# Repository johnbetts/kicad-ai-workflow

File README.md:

# kicad-ai-pipeline

AI-assisted KiCad EDA pipeline that takes hardware projects from natural-language requirements through to production-ready manufacturing files (Gerbers, BOM, CPL) for JLCPCB.

## What it does

1. **Requirements** — Define your board in plain English: components, connections, constraints
2. **Schematic** — Generates KiCad 10 hierarchical schematics with correct net assignment
3. **PCB Layout** — Places components using a 3-level EE-grade placement optimizer (zone partitioning, group placement, subcircuit refinement)
4. **Validation** — DRC, ERC, electrical checks, manufacturing checks, signal integrity
5. **Production** — Gerber, drill, BOM, CPL files ready for JLCPCB SMT assembly

Every stage outputs valid KiCad 10 files that open directly in KiCad.

## Install

```bash
pip install -e .
# or with dev dependencies:
pip install -e ".[dev]"
```

Requires Python 3.10+. No runtime dependencies for core pipeline.

## Quick start

```bash
# From a requirements JSON file:
kicad-pipeline build requirements.json --output-dir output/

# Or use the Python API:
python -c "
from kicad_pipeline.pcb.builder import build_pcb
from kicad_pipeline.models.requirements import ProjectRequirements
import json

req = ProjectRequirements.from_dict(json.load(open('requirements.json')))
pcb = build_pcb(req)
"
```

## Pipeline stages

| Stage | Module | Output |
|-------|--------|--------|
| Requirements | `requirements/` | `ProjectRequirements` dataclass |
| Parts enrichment | `parts/` | LCSC part numbers from JLCPCB 7M-part database |
| Schematic | `schematic/` | `.kicad_sch` files (hierarchical) |
| PCB layout | `pcb/` + `optimization/` | `.kicad_pcb` with placed components |
| Routing | `routing/` | Tracks and vias (grid router + FreeRouting) |
| Validation | `validation/` | DRC, ERC, electrical, manufacturing, thermal, SI reports |
| Production | `production/` | Gerbers, drill, BOM, CPL, assembly drawings |

## Project structure

```
src/kicad_pipeline/
  models/          # Frozen dataclasses: PCBDesign, ProjectRequirements, etc.
  sexp/            # KiCad S-expression parser and writer
  requirements/    # NL decomposition, component DB, pin/power budgets
  schematic/       # Schematic builder, symbols, subcircuits, wiring, ERC
  pcb/             # PCB builder, footprints, placement, netlist, zones
  optimization/    # EE placement optimizer (24 phases), scoring, review agent
  routing/         # Grid router, FreeRouting integration, DSN export
  validation/      # DRC, electrical, manufacturing, thermal, signal integrity
  production/      # Gerber, drill, BOM, CPL, assembly drawing, packager
  orchestrator/    # Multi-stage workflow engine with variant support
  github/          # Git ops, issues, releases, changelog
  cli/             # Command-line interface
tests/             # 2850+ tests (unit, integration, regression)
```

## Testing

```bash
pytest tests/ -x --tb=short          # Full suite
pytest tests/ -m "not slow"          # Fast tests only
pytest tests/ --cov=src/kicad_pipeline  # With coverage
```

## Code quality

```bash
mypy src/ --strict    # Type checking
ruff check src/ tests/  # Linting
ruff format src/ tests/ # Formatting
```

## JLCPCB compatibility

All components are validated against JLCPCB's parts catalog. The pipeline prefers basic parts (no setup fee) and verifies stock availability before generating production files.

## License

Apache License 2.0 — see [LICENSE](LICENSE).

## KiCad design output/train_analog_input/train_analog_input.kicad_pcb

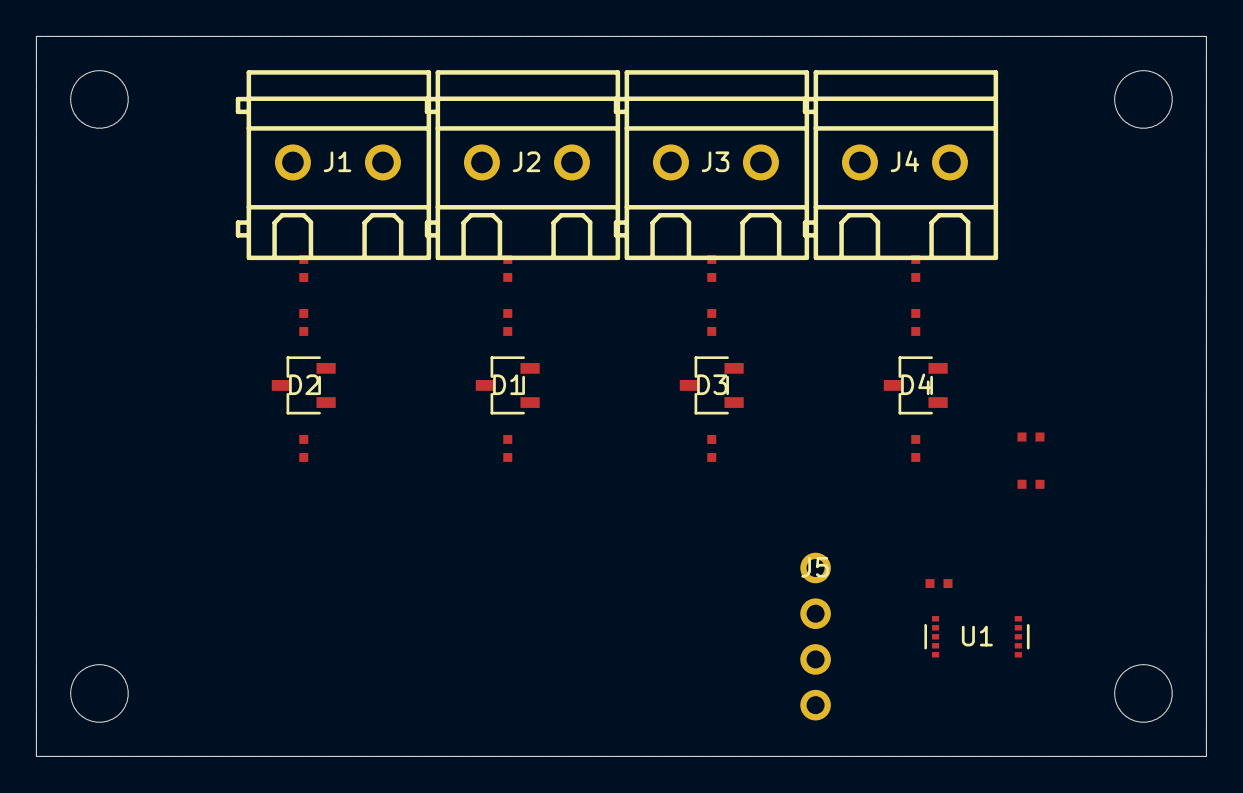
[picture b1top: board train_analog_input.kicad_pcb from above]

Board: 2 copper layers, 65.0 x 40.0 mm, 29 parts (0 on the bottom side), 17 nets, no tracks yet.

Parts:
C1, C2, C3, C4, C5: 100nF; C_0402_1005Metric
D1, D2, D3, D4: PESD3V3; SOT-23-3_L2.9-W1.6-P1.90-LS2.8-BR
H1, H2, H3, H4: MountingHole; MountingHole_2.7mm_M2.5
J1, J2, J3, J4: Screw_Terminal_2P; CONN-TH_2P-P5.00_WJ128V-5.0-2P
J5: PinHeader_1x04
R1, R2, R3, R4, R5, R6, R7, R8: 10K; R_0402_1005Metric
R9, R10: 4.7K; R_0402_1005Metric
U1: ADS1115; MSOP-10

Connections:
+3V3: J5.3, R9.1, R10.1
+3V3_U1_DEC: C1.1, U1.8
AIN1_DIV: R1.2, R2.1
AIN1_PROT: C2.1, D1.1, U1.5
AIN1_RAW: J1.1, R1.1
AIN2_DIV: R3.2, R4.1
AIN2_PROT: C3.1, D2.1, U1.4
AIN2_RAW: J2.1, R3.1
AIN3_DIV: R5.2, R6.1
AIN3_PROT: C4.1, D3.1, U1.6
AIN3_RAW: J3.1, R5.1
AIN4_DIV: R7.2, R8.1
AIN4_PROT: C5.1, D4.1, U1.7
AIN4_RAW: J4.1, R7.1
GND: C1.2, C2.2, C3.2, C4.2, C5.2, D1.2, D2.2, D3.2, D4.2, J1.2, J2.2, J3.2, J4.2, J5.4, R2.2, R4.2, R6.2, R8.2, U1.1, U1.3
SCL: J5.2, R10.2, U1.10
SDA: J5.1, R9.2, U1.9

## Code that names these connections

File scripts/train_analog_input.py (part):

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            Pin("1", "ADDR", PinType.INPUT, net="GND"),
            Pin("2", "ALERT", PinType.OUTPUT),  # no connect
            Pin("3", "GND", PinType.POWER_IN, PinFunction.GND, net="GND"),
            Pin("4", "AIN0", PinType.INPUT, PinFunction.ADC, net="AIN2_DIV"),
            Pin("5", "AIN1", PinType.INPUT, PinFunction.ADC, net="AIN1_DIV"),
            Pin("6", "AIN2", PinType.INPUT, PinFunction.ADC, net="AIN3_DIV"),
            Pin("7", "AIN3", PinType.INPUT, PinFunction.ADC, net="AIN4_DIV"),
            Pin("8", "VDD", PinType.POWER_IN, PinFunction.VCC, net="+3V3"),
            Pin("9", "SDA", PinType.BIDIRECTIONAL, PinFunction.I2C_SDA, net="SDA"),
            Pin("10", "SCL", PinType.INPUT, PinFunction.I2C_SCL, net="SCL"),
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
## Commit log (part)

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2026-03-26 Revert "pcb-review: iter1 — add proximity re-enforcement after all phases, update best_positions"
    This reverts commit df303ef5c5d20e900fe11075ca43fcf847e34613.
2026-03-31 fix(optimizer): force screw terminals to TOP edge, RJ45 to RIGHT, USB to BOTTOM
2026-03-31 fix(optimizer): don't override top-edge connectors during THT enforcement
2026-03-31 fix(optimizer): fix terminal block top-edge placement (use origin, not centroid)
2026-03-31 fix(optimizer): terminals ignore fixed_refs for top-edge placement
2026-03-31 fix(optimizer): 3b3 only grabs relay-group L/C, not all caps on board
    CRITICAL BUG: _phase_relay_power_isolation was claiming ALL capacitors
    and inductors (41 components) and dumping them at y=77. Now scoped to
    only components in the Relay Outputs feature block.
2026-03-31 feat(optimizer): simple 3-pass placement replacing 25 broken phases
    New algorithm: connectors→edges, ICs→zone centers, support→around ICs.
    Uses occupancy grid for collision-free placement during stamping.
    Wired behind level3='simple' flag (default). Old code preserved as
    level3='legacy'.
2026-04-04 Revert "fix(placement): aggressive push-apart achieves 0 collisions in centroid space"
    This reverts commit bf2187b957c93a5ed92d079e41b002ed5ab50252.
2026-04-04 Revert "feat(placement): collision guard + final resolution pass — 29→12 collisions"
    This reverts commit 555b05092b430d733b62a2002712e01787296676.
2026-04-04 Revert "fix(placement): chain-aware push-apart gets collisions to 4 (from 48)"
    This reverts commit f51bb1e42269f79305fc0fcb77d38bc161262b0a.
